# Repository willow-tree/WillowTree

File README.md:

# WillowTree
## Deploying to the BeagleBone
1. Connect to the Beaglebone using one of the below methods.
  - Connect through ethernet: `ssh root@<ip-address-of-connected-beagle-bone>`
  - Connect using a USB mini cable: `ssh root@192.168.7.2`
  - Connect using the serial device: `screen /dev/tty.usbmodem<somenumber> 115200`

2. From your local computer, copy over the entire WillowTree folder to the BeagleBone `/opt` directory.
  - `scp -r <WillowTree folder> root@<ip address from step1>:/opt`

3. SSH into the Beaglebone using whichever step you chose in Step 1.

4. CD into the `/opt` folder and rename the scp'd folder to `willow`

5. CD to the `/opt/willow/service`

6. Inside this `willow/service` folder, run `./install-service.sh`

NOTE: The folder name from which you are running `./install-service.sh` needs to be named `willow`. Otherwise, you need to update the routes in the `willow.service` file.

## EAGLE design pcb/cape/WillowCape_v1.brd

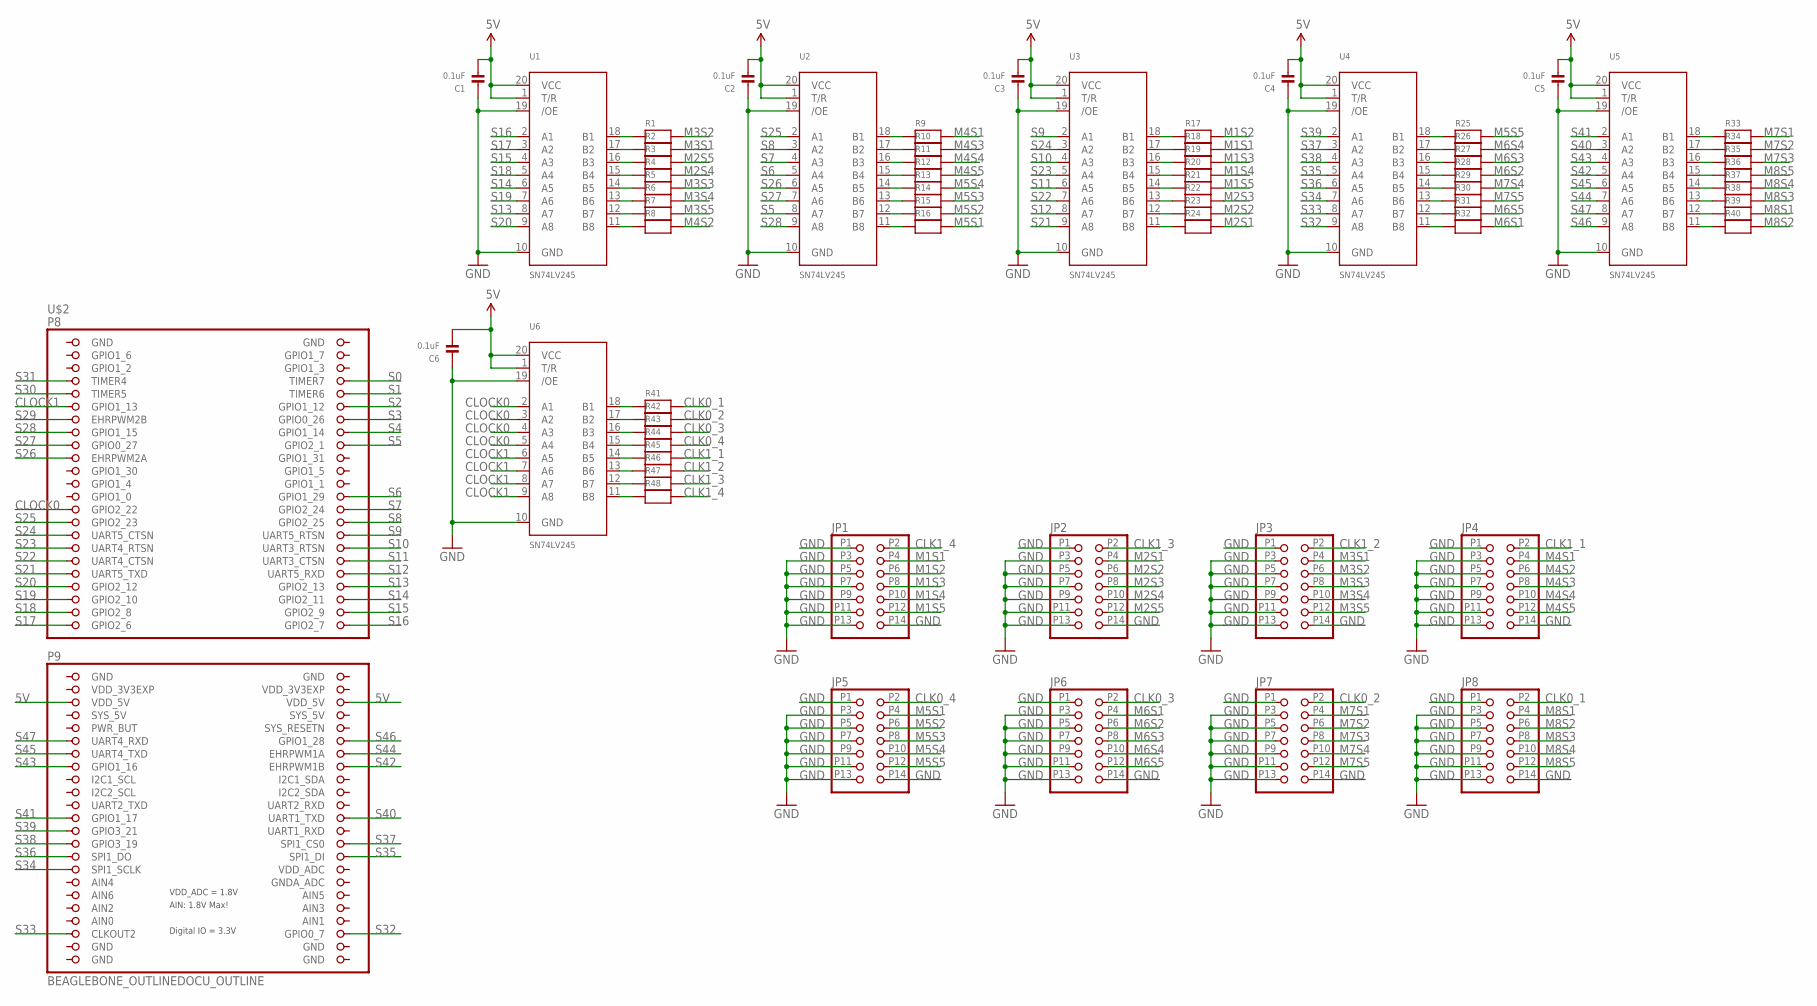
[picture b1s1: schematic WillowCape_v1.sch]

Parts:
C1, C2, C3, C4, C5, C6: 0.1uF; 0603
JP1, JP2, JP3, JP4, JP5, JP6, JP7, JP8: IDC-BOX-HEADER
R1, R2, R3, R4, R5, R6, R7, R8, R9, R10, R11, R12, R13, R14, R15, R16, R17, R18, R19, R20, R21, R22, R23, R24, R25, R26, R27, R28, R29, R30, R31, R32, R33, R34, R35, R36, R37, R38, R39, R40, R41, R42, R43, R44, R45, R46, R47, R48: RESISTOR0603; 0603
U1, U2, U3, U4, U5, U6: SN74LV245; TSSOP20
U$2: BEAGLEBONE_OUTLINEDOCU_OUTLINE; BEAGLEBONE_OUTLINE_DOCU

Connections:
5V: C1.2, C2.2, C3.2, C4.2, C5.2, C6.2, U1.1 (T/R), U1.20 (VCC), U2.1 (T/R), U2.20 (VCC), U3.1 (T/R), U3.20 (VCC), U4.1 (T/R), U4.20 (VCC), U5.1 (T/R), U5.20 (VCC), U6.1 (T/R), U6.20 (VCC), U$2.51 (VDD_5V), U$2.52 (VDD_5V)
CLK0_1: JP8.P2 (2), R41.2
CLK0_2: JP7.P2 (2), R42.2
CLK0_3: JP6.P2 (2), R43.2
CLK0_4: JP5.P2 (2), R44.2
CLK1_1: JP4.P2 (2), R45.2
CLK1_2: JP3.P2 (2), R46.2
CLK1_3: JP2.P2 (2), R47.2
CLK1_4: JP1.P2 (2), R48.2
CLOCK0: U6.2 (A1), U6.3 (A2), U6.4 (A3), U6.5 (A4), U$2.27 (GPIO2_22)
CLOCK1: U6.6 (A5), U6.7 (A6), U6.8 (A7), U6.9 (A8), U$2.11 (GPIO1_13)
GND: C1.1, C2.1, C3.1, C4.1, C5.1, C6.1, JP1.P1 (1), JP1.P3 (3), JP1.P5 (5), JP1.P7 (7), JP1.P9 (9), JP1.P11 (11), JP1.P13 (13), JP1.P14 (14), JP2.P1 (1), JP2.P3 (3), JP2.P5 (5), JP2.P7 (7), JP2.P9 (9), JP2.P11 (11), JP2.P13 (13), JP2.P14 (14), JP3.P1 (1), JP3.P3 (3), JP3.P5 (5), JP3.P7 (7), JP3.P9 (9), JP3.P11 (11), JP3.P13 (13), JP3.P14 (14), JP4.P1 (1), JP4.P3 (3), JP4.P5 (5), JP4.P7 (7), JP4.P9 (9), JP4.P11 (11), JP4.P13 (13), JP4.P14 (14), JP5.P1 (1), JP5.P3 (3), JP5.P5 (5), JP5.P7 (7), JP5.P9 (9), JP5.P11 (11), JP5.P13 (13), JP5.P14 (14), JP6.P1 (1), JP6.P3 (3), JP6.P5 (5), JP6.P7 (7), JP6.P9 (9), JP6.P11 (11), JP6.P13 (13), JP6.P14 (14), JP7.P1 (1), JP7.P3 (3), JP7.P5 (5), JP7.P7 (7), JP7.P9 (9), JP7.P11 (11), JP7.P13 (13), JP7.P14 (14), JP8.P1 (1), JP8.P3 (3), JP8.P5 (5), JP8.P7 (7), JP8.P9 (9), JP8.P11 (11), JP8.P13 (13), JP8.P14 (14), U1.10 (GND), U1.19 (/OE), U2.10 (GND), U2.19 (/OE), U3.10 (GND), U3.19 (/OE), U4.10 (GND), U4.19 (/OE), U5.10 (GND), U5.19 (/OE), U6.10 (GND), U6.19 (/OE), U$2.1 (GND), U$2.2 (GND), U$2.47 (GND), U$2.48 (GND), U$2.89 (GND), U$2.90 (GND), U$2.91 (GND), U$2.92 (GND)
GNDA_ADC: U$2.80 (GNDA_ADC)
M1S1: JP1.P4 (4), R18.2
M1S2: JP1.P6 (6), R17.2
M1S3: JP1.P8 (8), R19.2
M1S4: JP1.P10 (10), R20.2
M1S5: JP1.P12 (12), R21.2
M2S1: JP2.P4 (4), R24.2
M2S2: JP2.P6 (6), R23.2
M2S3: JP2.P8 (8), R22.2
M2S4: JP2.P10 (10), R4.2
M2S5: JP2.P12 (12), R3.2
M3S1: JP3.P4 (4), R2.2
M3S2: JP3.P6 (6), R1.2
M3S3: JP3.P8 (8), R5.2
M3S4: JP3.P10 (10), R6.2
M3S5: JP3.P12 (12), R7.2
M4S1: JP4.P4 (4), R9.2
M4S2: JP4.P6 (6), R8.2
M4S3: JP4.P8 (8), R10.2
M4S4: JP4.P10 (10), R11.2
M4S5: JP4.P12 (12), R12.2
M5S1: JP5.P4 (4), R16.2
M5S2: JP5.P6 (6), R15.2
M5S3: JP5.P8 (8), R14.2
M5S4: JP5.P10 (10), R13.2
M5S5: JP5.P12 (12), R25.2
M6S1: JP6.P4 (4), R32.2
M6S2: JP6.P6 (6), R28.2
M6S3: JP6.P8 (8), R27.2
M6S4: JP6.P10 (10), R26.2
M6S5: JP6.P12 (12), R31.2
M7S1: JP7.P4 (4), R33.2
M7S2: JP7.P6 (6), R34.2
M7S3: JP7.P8 (8), R35.2
M7S4: JP7.P10 (10), R29.2
M7S5: JP7.P12 (12), R30.2
M8S1: JP8.P4 (4), R39.2
M8S2: JP8.P6 (6), R40.2
M8S3: JP8.P8 (8), R38.2
M8S4: JP8.P10 (10), R37.2
M8S5: JP8.P12 (12), R36.2
unnamed: R1.1, U1.18 (B1)
unnamed: R2.1, U1.17 (B2)
unnamed: R3.1, U1.16 (B3)
unnamed: R4.1, U1.15 (B4)
unnamed: R5.1, U1.14 (B5)
unnamed: R6.1, U1.13 (B6)
unnamed: R7.1, U1.12 (B7)
unnamed: R8.1, U1.11 (B8)
unnamed: R9.1, U2.18 (B1)
unnamed: R10.1, U2.17 (B2)
unnamed: R11.1, U2.16 (B3)
unnamed: R12.1, U2.15 (B4)
unnamed: R13.1, U2.14 (B5)
unnamed: R14.1, U2.13 (B6)
unnamed: R15.1, U2.12 (B7)
unnamed: R16.1, U2.11 (B8)
unnamed: R17.1, U3.18 (B1)
unnamed: R18.1, U3.17 (B2)
unnamed: R19.1, U3.16 (B3)
unnamed: R20.1, U3.15 (B4)
unnamed: R21.1, U3.14 (B5)
unnamed: R22.1, U3.13 (B6)
unnamed: R23.1, U3.12 (B7)
unnamed: R24.1, U3.11 (B8)
unnamed: R25.1, U4.18 (B1)
unnamed: R26.1, U4.17 (B2)
unnamed: R27.1, U4.16 (B3)
unnamed: R28.1, U4.15 (B4)
unnamed: R29.1, U4.14 (B5)
unnamed: R30.1, U4.13 (B6)
unnamed: R31.1, U4.12 (B7)
unnamed: R32.1, U4.11 (B8)
unnamed: R33.1, U5.18 (B1)
unnamed: R34.1, U5.17 (B2)
unnamed: R35.1, U5.16 (B3)
unnamed: R36.1, U5.15 (B4)
unnamed: R37.1, U5.14 (B5)
unnamed: R38.1, U5.13 (B6)
unnamed: R39.1, U5.12 (B7)
unnamed: R40.1, U5.11 (B8)
unnamed: R41.1, U6.18 (B1)
unnamed: R42.1, U6.17 (B2)
unnamed: R43.1, U6.16 (B3)
unnamed: R44.1, U6.15 (B4)
unnamed: R45.1, U6.14 (B5)
unnamed: R46.1, U6.13 (B6)
unnamed: R47.1, U6.12 (B7)
unnamed: R48.1, U6.11 (B8)
S0: U$2.8 (TIMER7)
S1: U$2.10 (TIMER6)
S2: U$2.12 (GPIO1_12)
S3: U$2.14 (GPIO0_26)
S4: U$2.16 (GPIO1_14)
S5: U2.8 (A7), U$2.18 (GPIO2_1)
S6: U2.5 (A4), U$2.26 (GPIO1_29)
S7: U2.4 (A3), U$2.28 (GPIO2_24)
S8: U2.3 (A2), U$2.30 (GPIO2_25)
S9: U3.2 (A1), U$2.32 (UART5_RTSN)
S10: U3.4 (A3), U$2.34 (UART3_RTSN)
S11: U3.6 (A5), U$2.36 (UART3_CTSN)
S12: U3.8 (A7), U$2.38 (UART5_RXD)
S13: U1.8 (A7), U$2.40 (GPIO2_13)
S14: U1.6 (A5), U$2.42 (GPIO2_11)
S15: U1.4 (A3), U$2.44 (GPIO2_9)
S16: U1.2 (A1), U$2.46 (GPIO2_7)
S17: U1.3 (A2), U$2.45 (GPIO2_6)
S18: U1.5 (A4), U$2.43 (GPIO2_8)
S19: U1.7 (A6), U$2.41 (GPIO2_10)
S20: U1.9 (A8), U$2.39 (GPIO2_12)
S21: U3.9 (A8), U$2.37 (UART5_TXD)
S22: U3.7 (A6), U$2.35 (UART4_CTSN)
S23: U3.5 (A4), U$2.33 (UART4_RTSN)
S24: U3.3 (A2), U$2.31 (UART5_CTSN)
S25: U2.2 (A1), U$2.29 (GPIO2_23)
S26: U2.6 (A5), U$2.19 (EHRPWM2A)
S27: U2.7 (A6), U$2.17 (GPIO0_27)
S28: U2.9 (A8), U$2.15 (GPIO1_15)
S29: U$2.13 (EHRPWM2B)
S30: U$2.9 (TIMER5)
S31: U$2.7 (TIMER4)
S32: U4.9 (A8), U$2.88 (GPIO0_7)
S33: U4.8 (A7), U$2.87 (CLKOUT2)
S34: U4.7 (A6), U$2.77 (SPI1_SCLK)
S35: U4.5 (A4), U$2.76 (SPI1_DI)
S36: U4.6 (A5), U$2.75 (SPI1_DO)
S37: U4.3 (A2), U$2.74 (SPI1_CS0)
S38: U4.4 (A3), U$2.73 (GPIO3_19)
S39: U4.2 (A1), U$2.71 (GPIO3_21)
S40: U5.3 (A2), U$2.70 (UART1_TXD)
S41: U5.2 (A1), U$2.69 (GPIO1_17)
S42: U5.5 (A4), U$2.62 (EHRPWM1B)
S43: U5.4 (A3), U$2.61 (GPIO1_16)
S44: U5.7 (A6), U$2.60 (EHRPWM1A)
S45: U5.6 (A5), U$2.59 (UART4_TXD)
S46: U5.9 (A8), U$2.58 (GPIO1_28)
S47: U5.8 (A7), U$2.57 (UART4_RXD)
SYS_5V: U$2.53 (SYS_5V), U$2.54 (SYS_5V)
VDD_3V3EXP: U$2.49 (VDD_3V3EXP), U$2.50 (VDD_3V3EXP)
VDD_ADC: U$2.78 (VDD_ADC)

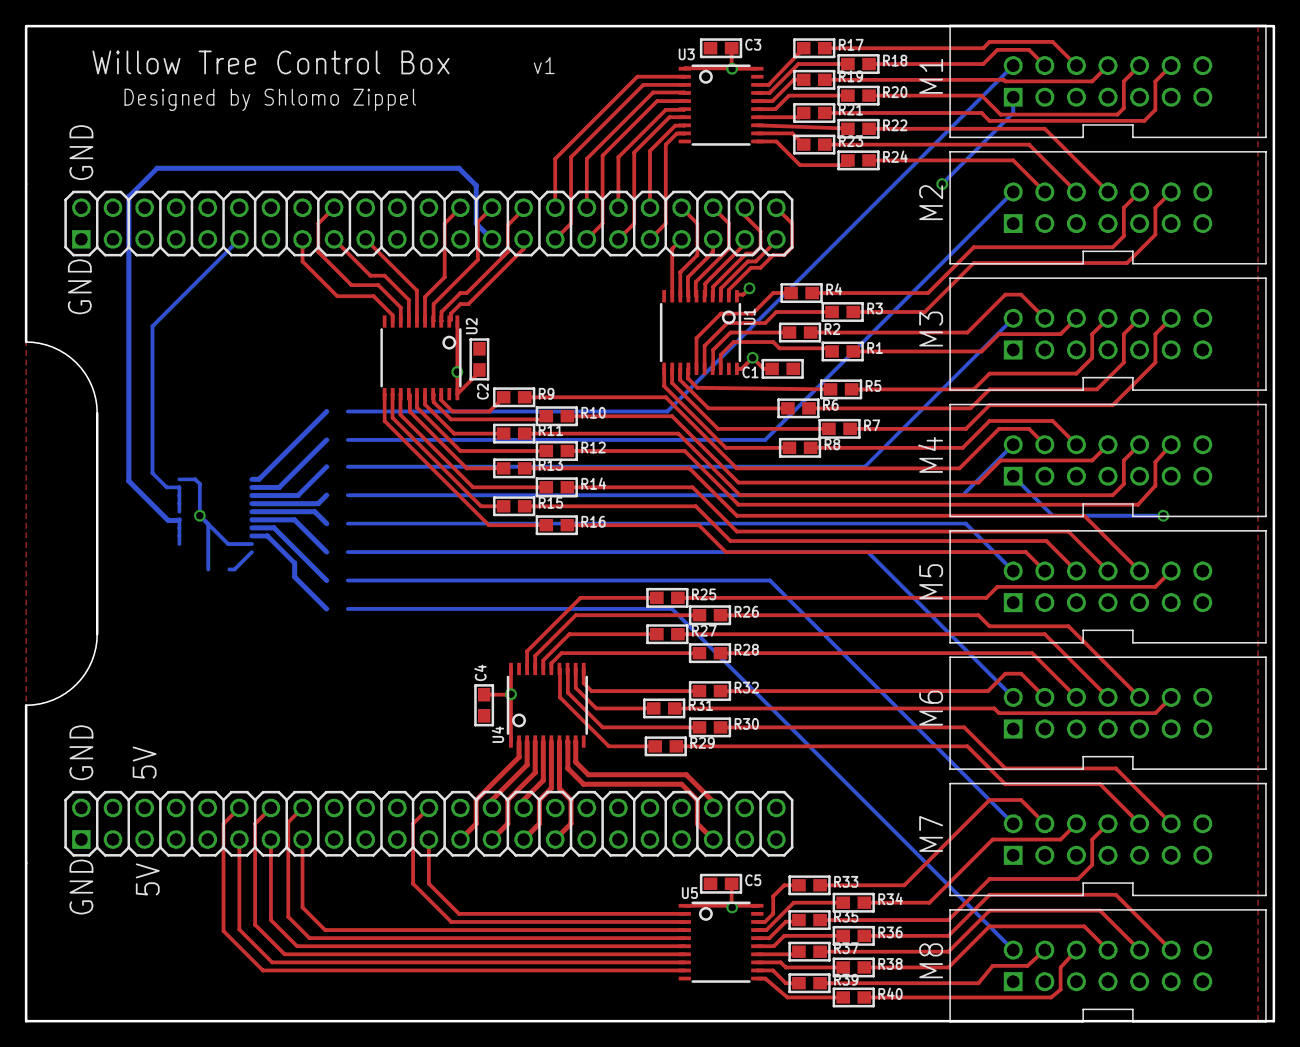
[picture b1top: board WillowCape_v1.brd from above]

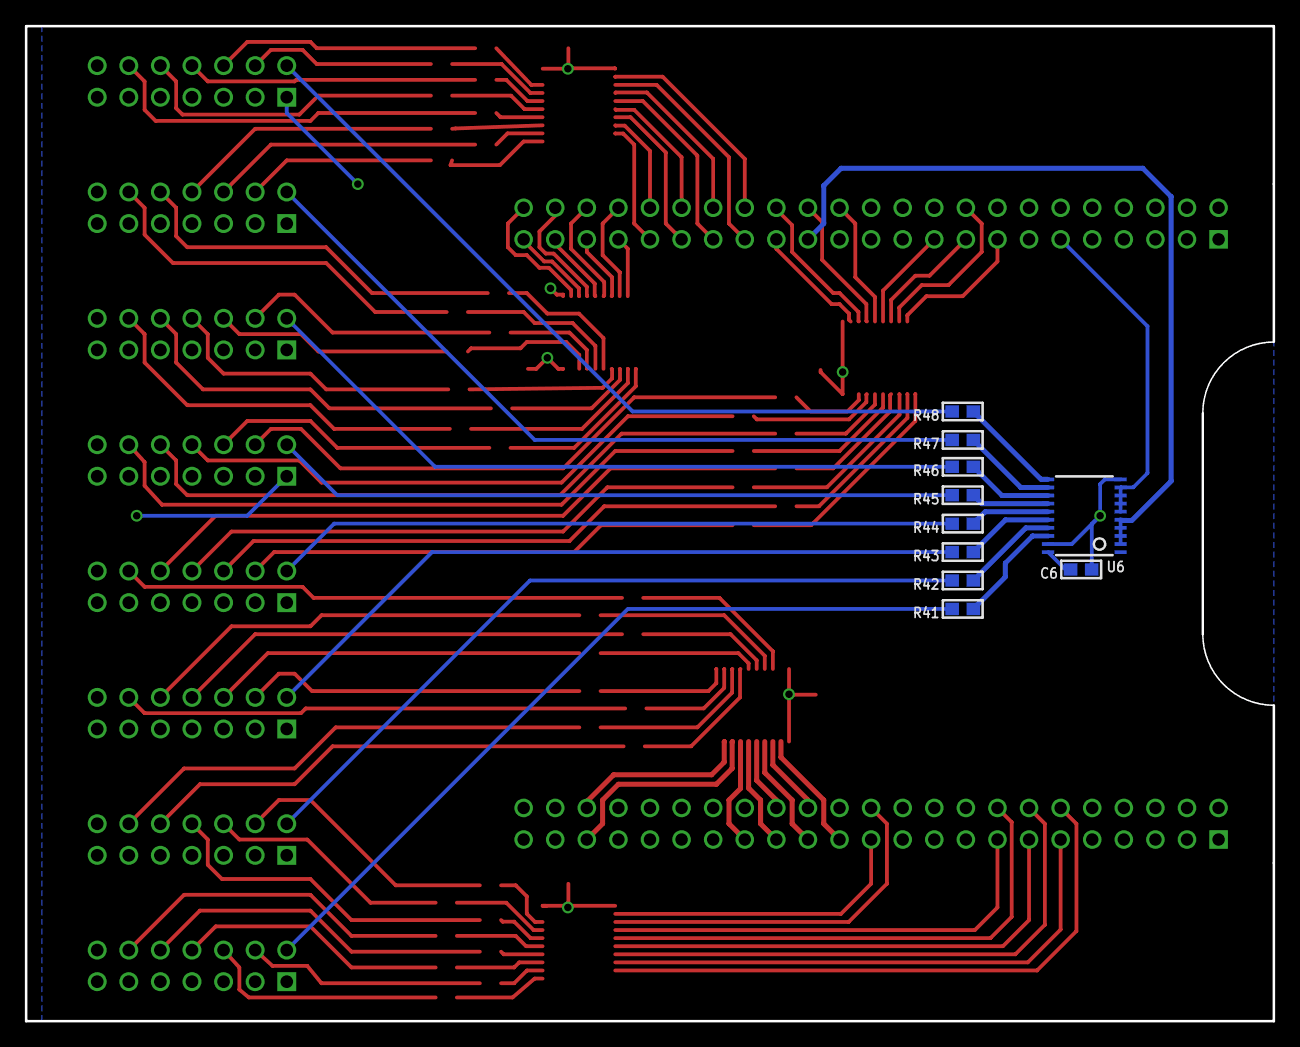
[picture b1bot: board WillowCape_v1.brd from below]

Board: 2 copper layers, 100.3 x 80.0 mm, 69 parts (10 on the bottom side), 142 nets.

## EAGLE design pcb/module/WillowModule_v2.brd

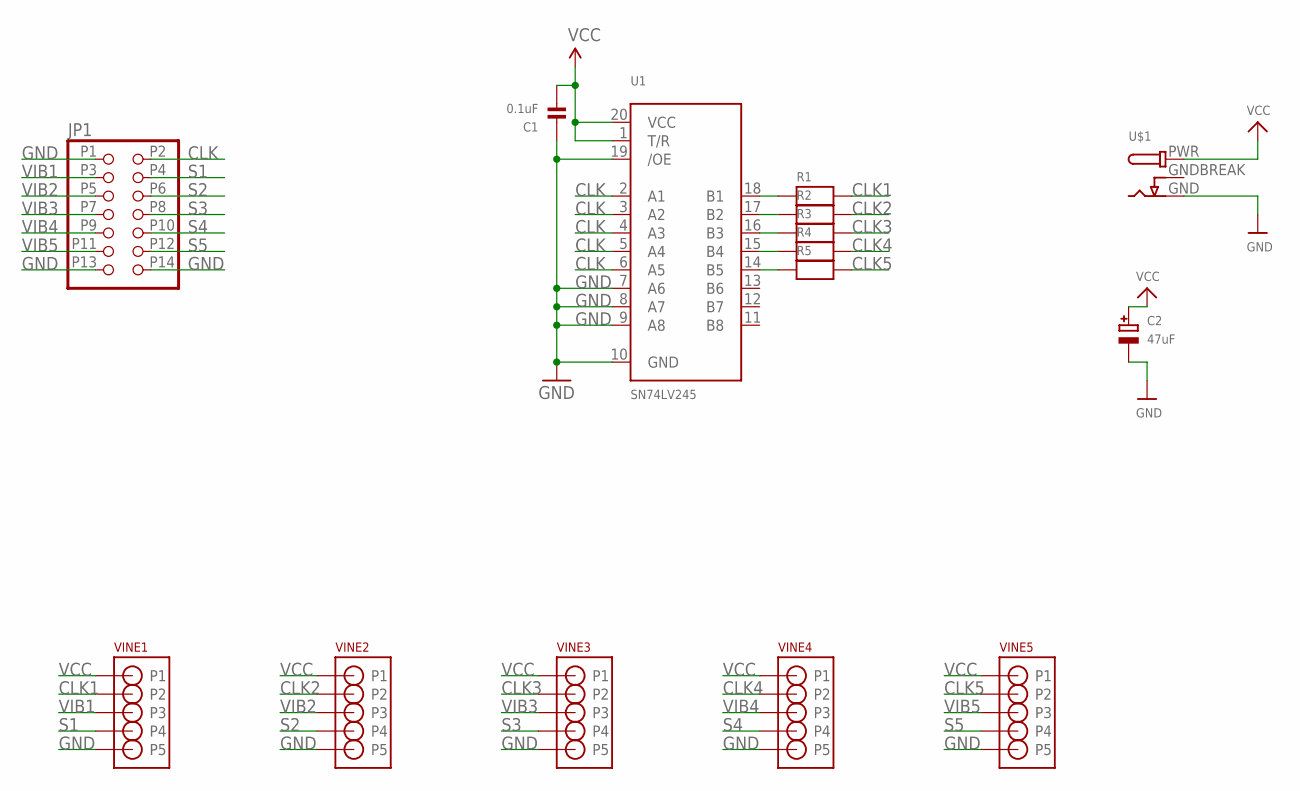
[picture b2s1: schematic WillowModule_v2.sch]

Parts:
C1: 0.1uF; 0603
C2: 47uF; PANASONIC_C
JP1: IDC-BOX-HEADER
R1, R2, R3, R4, R5: RESISTOR0603; 0603
U1: SN74LV245; TSSOP20
U$1: DC-POWER-JACK-3PIN; PJ-050AH
VINE1, VINE2, VINE3, VINE4, VINE5: DIN-5PIN-180SDS-50J; SDS-50J

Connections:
CLK: JP1.P2 (2), U1.2 (A1), U1.3 (A2), U1.4 (A3), U1.5 (A4), U1.6 (A5)
CLK1: R1.2, VINE1.P2
CLK2: R2.2, VINE2.P2
CLK3: R3.2, VINE3.P2
CLK4: R4.2, VINE4.P2
CLK5: R5.2, VINE5.P2
GND: C1.1, C2.-, JP1.P1 (1), JP1.P13 (13), JP1.P14 (14), U1.7 (A6), U1.8 (A7), U1.9 (A8), U1.10 (GND), U1.19 (/OE), U$1.GND, VINE1.P5, VINE2.P5, VINE3.P5, VINE4.P5, VINE5.P5
GNDBREAK: U$1.GNDBREAK
unnamed: R1.1, U1.18 (B1)
unnamed: R2.1, U1.17 (B2)
unnamed: R3.1, U1.16 (B3)
unnamed: R4.1, U1.15 (B4)
unnamed: R5.1, U1.14 (B5)
S1: JP1.P4 (4), VINE1.P4
S2: JP1.P6 (6), VINE2.P4
S3: JP1.P8 (8), VINE3.P4
S4: JP1.P10 (10), VINE4.P4
S5: JP1.P12 (12), VINE5.P4
VCC: C1.2, C2.+, U1.1 (T/R), U1.20 (VCC), U$1.PWR, VINE1.P1, VINE2.P1, VINE3.P1, VINE4.P1, VINE5.P1
VIB1: JP1.P3 (3), VINE1.P3
VIB2: JP1.P5 (5), VINE2.P3
VIB3: JP1.P7 (7), VINE3.P3
VIB4: JP1.P9 (9), VINE4.P3
VIB5: JP1.P11 (11), VINE5.P3

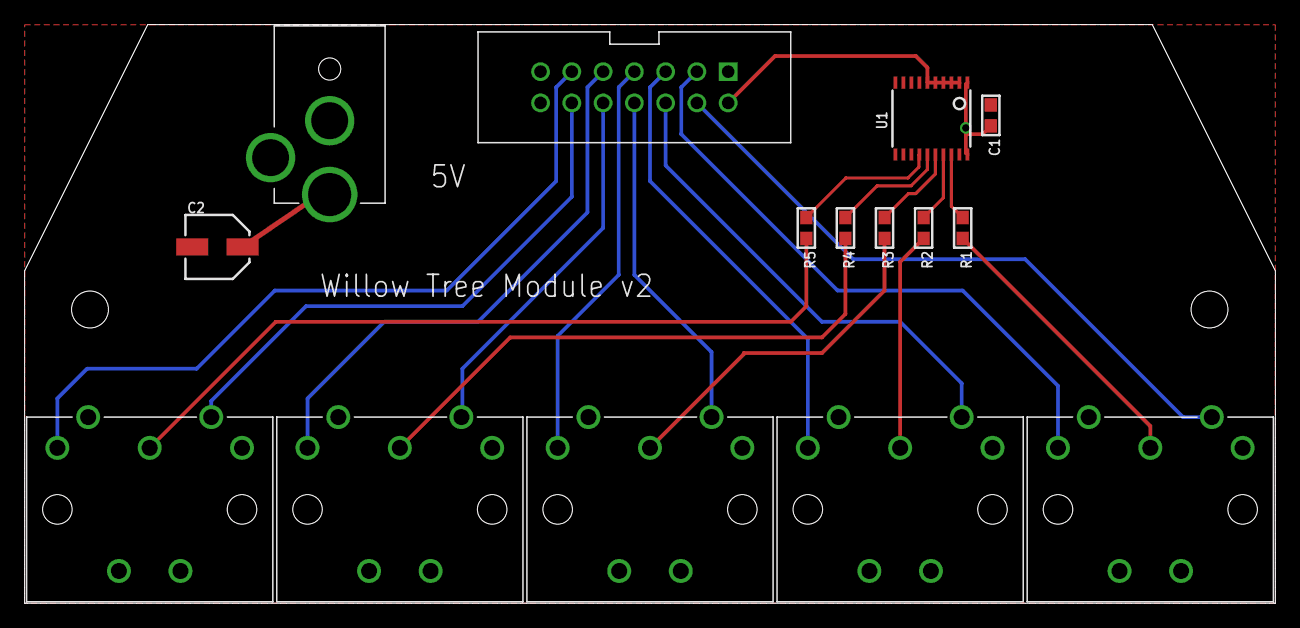
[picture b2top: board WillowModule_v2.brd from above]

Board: 2 copper layers, 101.6 x 47.0 mm, 15 parts (0 on the bottom side), 23 nets.

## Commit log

2015-07-02 First attempt, clock lines on top
2015-07-02 Done with v1 of control box. Motion sensors aren't connected yet but there are placeholders
2015-07-03 Added module
2015-07-03 Added mounting holes
2015-07-03 Minor fixes to silkscreen
2015-07-03 More fixes to silkscreen
2015-07-28 v2 of module pcb, made a bunch of fixes
2015-08-15 moved pcb files
2015-08-15 initial service stuff
2015-08-15 sane folder structure
2015-08-15 More scaffolding
2015-08-15 Adding some common methods, constants, and adding some patterns (nyan, plaid).
2015-08-23 Adding a watchdog type script to catch and silently fail errors.
2015-08-24 Adding fading~
2015-08-24 Fixing nyan.
2015-08-24 Changed service path
2015-08-25 Fixing the floor to be grey.
2015-08-25 Fixing the lavalamp to have less black patches.
2015-08-25 Removing old tree code, unneeded.
2016-08-21 added runner file which shows how to use sparkle stuff
2016-08-21 began refactoring constants & patterns into their own source files
2016-08-22 update to pattern infastructure .. still testing .. initial commit of structure
2016-08-22 Cleaning up the constants file. Adding new joinable functions to create patterns (courtesy Benjamin Johnson).
2016-08-22 Fixing constants.
2016-08-22 added period to cosine functions
2016-08-22 reorganized library and test patterns
2016-08-22 Code cleanup.
2016-08-22 fixes to library and test_patterns
2016-08-23 added new make it rain pattern
2016-08-23 latest updates .. starting merge pattern
2016-08-23 Upgrading from Python 2 to Python 3.
2016-08-23 python 3, we added transitions, made a rain transition
2016-08-23 added fireworks draft
2016-08-23 updated run-tree to use python3
2016-08-24 updated library and fireworks pattern, increased pattern times
2016-08-24 increased speed of make_it_rain
2016-08-24 Updating README with BeagleBone Black deploy instructions.
2016-08-24 Fixing formatting of README
2016-08-28 second version for the tree
2017-08-11 changes to runner.py and removing fireworks
2017-08-23 adding temporary file to tweak patterns
2017-08-23 tweaked pattens and transitions
2017-08-23 more tweaks to test_patterns
2017-08-24 added a comment for the server ip address to send to tree over usb
2017-09-06 version for tree BM2017

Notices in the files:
parts and their libraries:
microbuilder: This work is placed in the public domain, and may be freely used for commercial and non-commercial work with the following conditions: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
SparkFun-Aesthetics: Licensing: Creative Commons ShareAlike 4.0 International - https://creativecommons.org/licenses/by-sa/4.0
